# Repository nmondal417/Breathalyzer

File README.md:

# Breathalyzer Project Overview

The overall goal of this project is to create a wireless device that can be used to analyze the breath of medical patients to diagnose various diseases. The underlying technology is a graphene FET array. When the graphene FETs come into contact with different gases, the properties of the FETs will change. For example, the IDS vs VGS curve of the graphene FET may shift depending on the concentration of a certain gas molecule in the patient's breath. 

This GitHub project contains the PCBs and the code that are used to control and measure the graphene FET array. In simple terms, the PCB generates analog voltages VDS and VGS, and sends these to the graphene FET. Two multiplexers are used to select one particular FET out of the array. The PCB then measures the resulting IDS on that FET. This process is then repeated for every FET in the array, and then for different VDS and VGS. A python script can be used to plot the various voltage vs current curves.

# Device Design

The device is split into two chambers. The top chamber contains the graphene FET chip, an interface PCB for connecting to the chip, a humdity sensor, and a heater to prevent condensation on the chip. The bottom chamber contains most of the control electronics, inlucding the ESP32 micronctroller, the amplifiers, and multiplexers. There is also a single-cell 2 Ah LiPo for powering all the electronics, and a boost converter for specifically powering the heater. The LiPo can be charged through the USB-C connector located on the bottom of the device; when charging, the device will automatically turn off. 

On the outside of the device, there are various switches to control and LEDs to monitor the breathalyzer status. The main on switch connects the LiPo to the system and turns everything except the heater on; the heater on switch controls the heater. An RGB charge status LED lights up when the device is being charged; an orange light indicates that charging is occurring, while a white light indicates that charging is completed. Finally a "BLOW" LED controlled by the ESP32 indicates to the patient when they should blow into the device.

# PCBs

## ESP32 Carrier

https://github.com/nmondal417/Breathalyzer/tree/main/New%20PCB/Breathalyzer_ESP32

This PCB is where the ESP32, the main microcontroller, mounts **(NOTE: make sure to place the ESP32 correctly! the USB connector should face the side labeled "FRONT")**. The ESP32 controls the DAC, the ADC, and the multiplexers. It can also read data from the humidity sensor and the heater thermistor. It reports the current measurements in either serial or Bluetooth serial. 

The carrier board also contains the LiPo charge controller, the USB-C charging port, and the main 3.3V regulator that powers most of the ICs. All of the buttons and switches plug into the ESP32 carrrier board.

## Amplifier

https://github.com/nmondal417/Breathalyzer/tree/main/New%20PCB/Breathalyzer_Power%2BICs

This PCB contains the DAC, the ADC, and the op-amps that amplify the gate voltages.

The DAC (AD5328) communicates with the ESP32 over SPI. The DAC generates 6 gate voltages and 1 drain voltage. These voltages are in the range of 0 to 2 V; however, since the source voltage of this system is 1 V, the VGS and VDS voltages are actually -1 to +1 V. 

The op-amps then buffer and amplify the gate voltages. The op-amps can either provide x1 amplification (where it just acts a buffer), or x10 amplifcation. This amplification is controlled by the ESP32. The ESP32 controls two solid-state switches (ADG5433), which can change the amplifer gain by switching in a feedback resistor connected across the op-amp. The post-amplifcation gate voltage can be from -10 to +10 V.

The ADC (AD7274) communicates with the ESP32 over SPI. The ADC input is the voltage from the transimpedance amplifier. The ADC reads in range of 0 to 2V, and sends the ESP32 a 12-bit digital reading. 

This PCB also contains the 1V and 2V regulators that generate reference voltages for the DAC, ADC, and the op-amps, as well as a dual DC/DC converter (LT1945) that generates the -11V and +11V rails used for the amplifiers.

Finally, there is a mechanical switch that can completely disconnect the gate voltages from the graphene chip. This is useful for quickly turning off a voltage sweep, since if the incorrect gate voltages are accidentally applied the FET array can be destroyed.

## Multiplexer

https://github.com/nmondal417/Breathalyzer/tree/main/New%20PCB/Breathalyzer_Mux%2BConn

This PCB contains the two main multiplexers, the ribbon cable connector, and the transimpedance amplifier. 

The multiplexers are the ADG732. One is the drain demultiplexer, which sends the drain voltage to 1 of the 32 rows of the FET array. The other is the source muliplexer, which measures the source current from 1 of the 32 columns. 

The ribbon cable connector connects to the ribbon cable that runs from this PCB to the chip interface board. This cable is the PCB's connection to the drain, gate, and source terminals on the FET array.

The transimpedance ampliifer is an op-amp that is used to convert the source current measurement into a voltage. The formula is VMEAS = 1 - 1000*IDS, so an IDS of 100 uA would result in a VMEAS of 0.9V. This VMEAS is sent to the ADC.

# Code

All the code for this version of the breathlyzer is under 'New PCB code.' While the main code that runs on the ESP32 during normal operation is IV_Array_main_NEW, there are other files that test specific parts of the system, like the DAC and ADC, and are helpful for debugging.

## Blink

Simple test to just check if code can be uploaded correctly to the ESP32.

## ADC_DAC_test

This test can be used to test the ADC, DAC, or both together. Bascially, write analog voltages using the DAC and read an analog voltage using the ADC. If you are testing both the DAC and ADC at the same time, connect one of the DAC's output voltages to the input of the ADC.

## offset_and_gain_test

Used for checking and adjusting for the offset or gain error of the ADC and DAC. Test each DAC channel by connecting it to the ADC, and compare the read voltages to the expected values.

## gate_voltage_test

Tests that gate voltages can be generated properly. Combines the DAC code along with additional code to turn on the gate amplifier power supply and control the amplification.

## multiplexer_test

Close to a full system test, but instead of having the actual graphene array connected, you connect a test resistor between a drain connection on one mux and source connection on the other. When the correct select bits are sent to the muxes, the code should report the resistor value.

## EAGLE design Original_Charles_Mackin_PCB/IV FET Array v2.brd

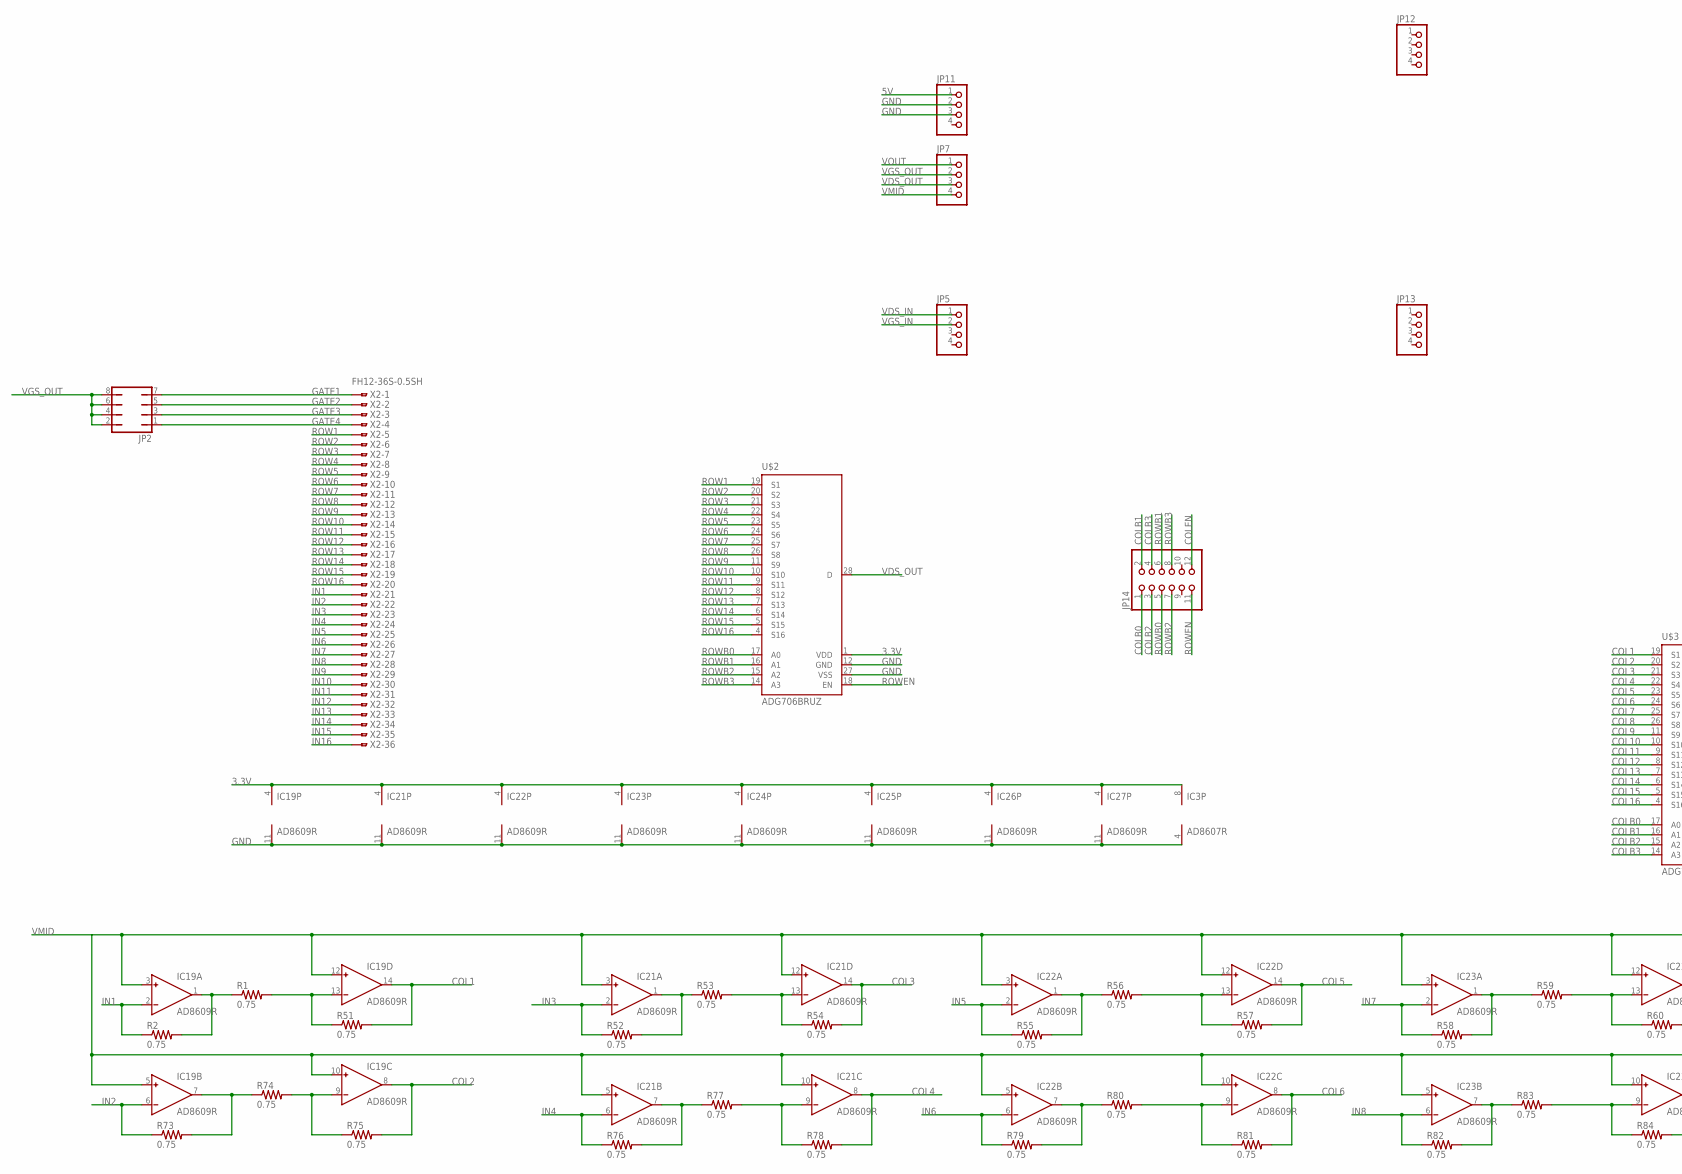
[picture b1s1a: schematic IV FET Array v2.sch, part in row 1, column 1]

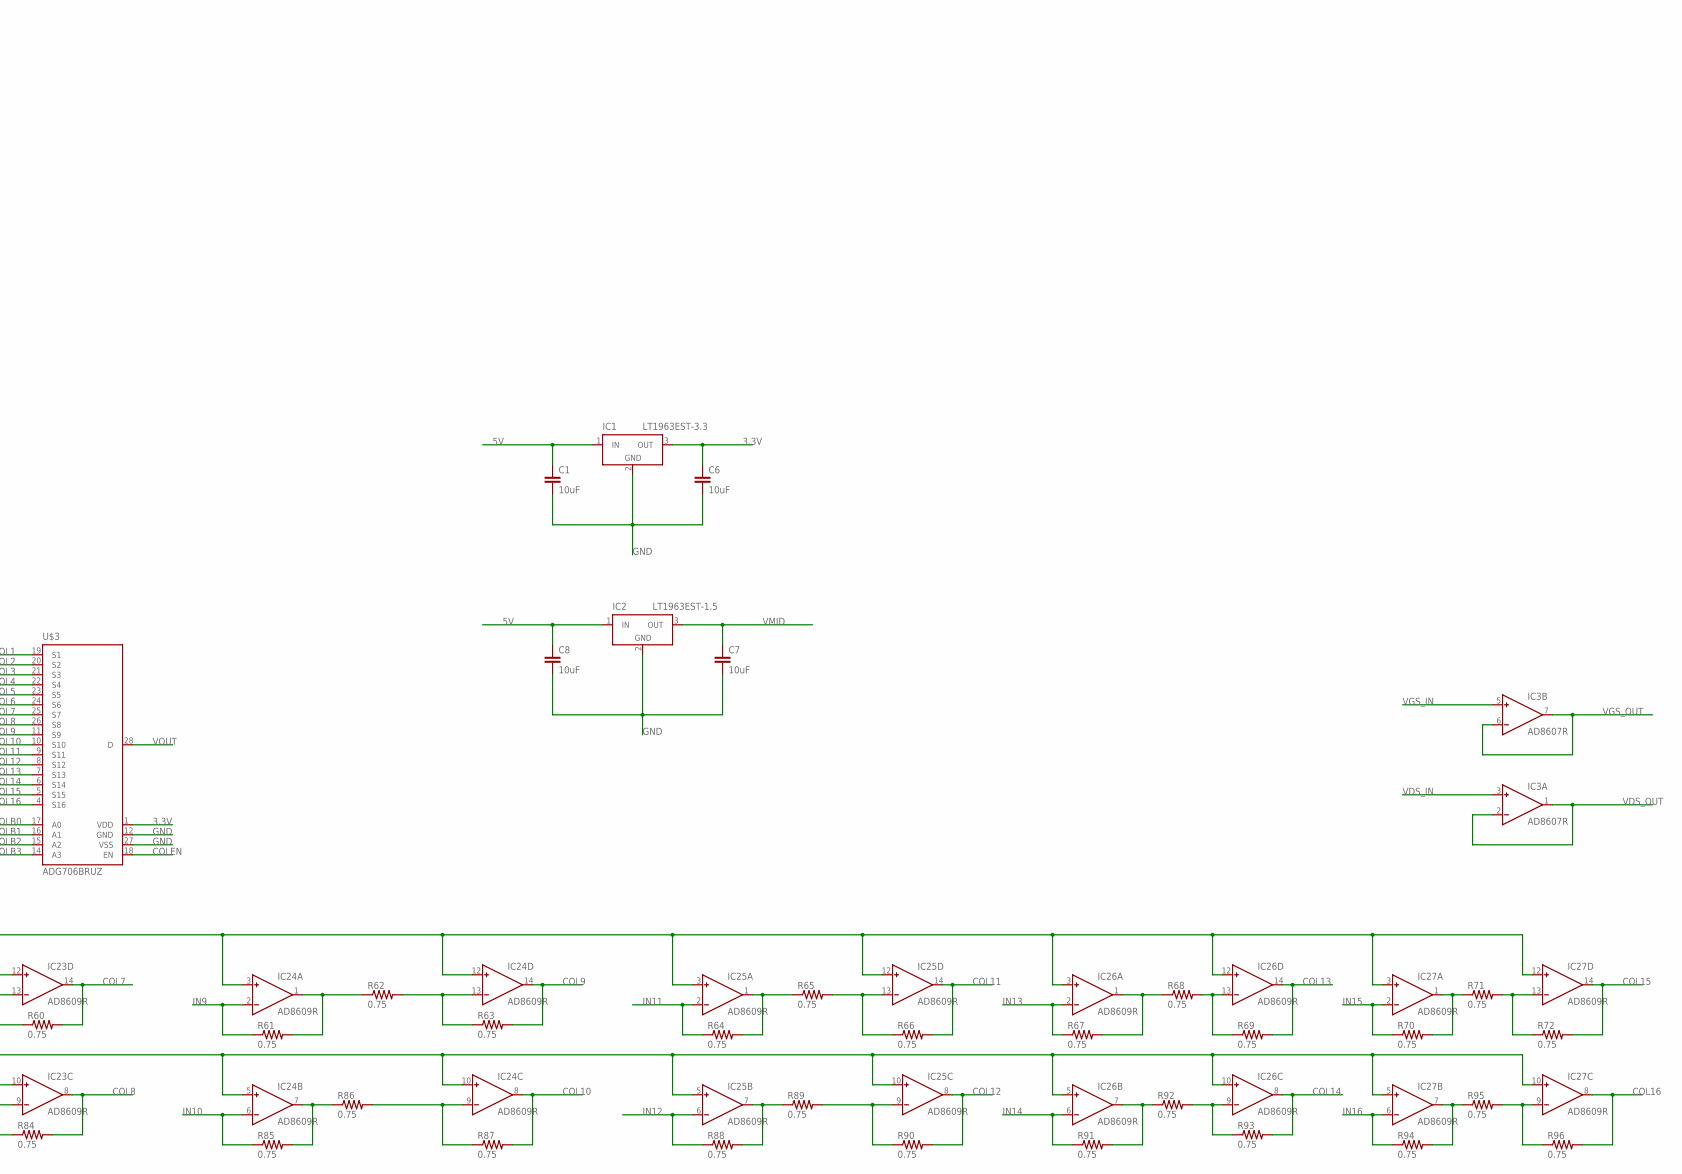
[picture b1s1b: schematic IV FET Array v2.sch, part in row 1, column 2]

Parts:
C1, C6, C7, C8: 10uF; 1210
IC1: LT1963EST-3.3; SOT223
IC2: LT1963EST-1.5; SOT223
IC3: AD8607R; SO8
IC19, IC21, IC22, IC23, IC24, IC25, IC26, IC27: AD8609R; SO14
JP2: JP4Q
JP5, JP7, JP11, JP12, JP13: PINHD-1X4; 1X04
JP14: PINHD-2X6; 2X06
R1, R2, R51, R52, R53, R54, R55, R56, R57, R58, R59, R60, R61, R62, R63, R64, R65, R66, R67, R68, R69, R70, R71, R72, R73, R74, R75, R76, R77, R78, R79, R80, R81, R82, R83, R84, R85, R86, R87, R88, R89, R90, R91, R92, R93, R94, R95, R96: 0.75; 0805
U$2, U$3: ADG706BRUZ; TSSOP28
X2: FH12-36S-0.5SH

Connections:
3.3V: C6.1, IC1.3 (OUT), IC3.8 (V+), IC19.4 (V+), IC21.4 (V+), IC22.4 (V+), IC23.4 (V+), IC24.4 (V+), IC25.4 (V+), IC26.4 (V+), IC27.4 (V+), U$2.1 (VDD), U$3.1 (VDD)
5V: C1.1, C8.1, IC1.1 (IN), IC2.1 (IN), JP11.1
COL1: IC19.14 (OUT), R51.2, U$3.19 (S1)
COL2: IC19.8 (OUT), R75.2, U$3.20 (S2)
COL3: IC21.14 (OUT), R54.2, U$3.21 (S3)
COL4: IC21.8 (OUT), R78.2, U$3.22 (S4)
COL5: IC22.14 (OUT), R57.2, U$3.23 (S5)
COL6: IC22.8 (OUT), R81.2, U$3.24 (S6)
COL7: IC23.14 (OUT), R60.2, U$3.25 (S7)
COL8: IC23.8 (OUT), R84.2, U$3.26 (S8)
COL9: IC24.14 (OUT), R63.2, U$3.11 (S9)
COL10: IC24.8 (OUT), R87.2, U$3.10 (S10)
COL11: IC25.14 (OUT), R66.2, U$3.9 (S11)
COL12: IC25.8 (OUT), R90.2, U$3.8 (S12)
COL13: IC26.14 (OUT), R69.2, U$3.7 (S13)
COL14: IC26.8 (OUT), R93.2, U$3.6 (S14)
COL15: IC27.14 (OUT), R72.2, U$3.5 (S15)
COL16: IC27.8 (OUT), R96.2, U$3.4 (S16)
COLB0: JP14.1, U$3.17 (A0)
COLB1: JP14.2, U$3.16 (A1)
COLB2: JP14.3, U$3.15 (A2)
COLB3: JP14.4, U$3.14 (A3)
COLEN: JP14.12, U$3.18 (EN)
GATE1: JP2.7, X2.1
GATE2: JP2.5, X2.2
GATE3: JP2.3, X2.3
GATE4: JP2.1, X2.4
GND: C1.2, C6.2, C7.2, C8.2, IC1.2 (GND), IC1.4 (GND), IC2.2 (GND), IC2.4 (GND), IC3.4 (V-), IC19.11 (V-), IC21.11 (V-), IC22.11 (V-), IC23.11 (V-), IC24.11 (V-), IC25.11 (V-), IC26.11 (V-), IC27.11 (V-), JP11.2, JP11.3, U$2.12 (GND), U$2.27 (VSS), U$3.12 (GND), U$3.27 (VSS)
IN1: IC19.2 (IN-), R2.1, X2.21
IN2: IC19.6 (IN-), R73.1, X2.22
IN3: IC21.2 (IN-), R52.1, X2.23
IN4: IC21.6 (IN-), R76.1, X2.24
IN5: IC22.2 (IN-), R55.1, X2.25
IN6: IC22.6 (IN-), R79.1, X2.26
IN7: IC23.2 (IN-), R58.1, X2.27
IN8: IC23.6 (IN-), R82.1, X2.28
IN9: IC24.2 (IN-), R61.1, X2.29
IN10: IC24.6 (IN-), R85.1, X2.30
IN11: IC25.2 (IN-), R64.1, X2.31
IN12: IC25.6 (IN-), R88.1, X2.32
IN13: IC26.2 (IN-), R67.1, X2.33
IN14: IC26.6 (IN-), R91.1, X2.34
IN15: IC27.2 (IN-), R70.1, X2.35
IN16: IC27.6 (IN-), R94.1, X2.36
unnamed: IC25.1 (OUT), R64.2, R65.1
unnamed: IC25.13 (IN-), R65.2, R66.1
unnamed: IC24.1 (OUT), R61.2, R62.1
unnamed: IC24.13 (IN-), R62.2, R63.1
unnamed: IC25.7 (OUT), R88.2, R89.1
unnamed: IC25.9 (IN-), R89.2, R90.1
unnamed: IC24.9 (IN-), R86.2, R87.1
unnamed: IC24.7 (OUT), R85.2, R86.1
unnamed: IC19.1 (OUT), R1.1, R2.2
unnamed: IC19.7 (OUT), R73.2, R74.1
unnamed: IC19.9 (IN-), R74.2, R75.1
unnamed: IC19.13 (IN-), R1.2, R51.1
unnamed: IC23.13 (IN-), R59.2, R60.1
unnamed: IC23.1 (OUT), R58.2, R59.1
unnamed: IC21.1 (OUT), R52.2, R53.1
unnamed: IC21.13 (IN-), R53.2, R54.1
unnamed: IC22.1 (OUT), R55.2, R56.1
unnamed: IC22.13 (IN-), R56.2, R57.1
unnamed: IC23.9 (IN-), R83.2, R84.1
unnamed: IC23.7 (OUT), R82.2, R83.1
unnamed: IC22.9 (IN-), R80.2, R81.1
unnamed: IC22.7 (OUT), R79.2, R80.1
unnamed: IC21.9 (IN-), R77.2, R78.1
unnamed: IC21.7 (OUT), R76.2, R77.1
unnamed: IC26.1 (OUT), R67.2, R68.1
unnamed: IC26.13 (IN-), R68.2, R69.1
unnamed: IC26.9 (IN-), R92.2, R93.1
unnamed: IC26.7 (OUT), R91.2, R92.1
unnamed: IC27.7 (OUT), R94.2, R95.1
unnamed: IC27.9 (IN-), R95.2, R96.1
unnamed: IC27.13 (IN-), R71.2, R72.1
unnamed: IC27.1 (OUT), R70.2, R71.1
ROW1: U$2.19 (S1), X2.5
ROW2: U$2.20 (S2), X2.6
ROW3: U$2.21 (S3), X2.7
ROW4: U$2.22 (S4), X2.8
ROW5: U$2.23 (S5), X2.9
ROW6: U$2.24 (S6), X2.10
ROW7: U$2.25 (S7), X2.11
ROW8: U$2.26 (S8), X2.12
ROW9: U$2.11 (S9), X2.13
ROW10: U$2.10 (S10), X2.14
ROW11: U$2.9 (S11), X2.15
ROW12: U$2.8 (S12), X2.16
ROW13: U$2.7 (S13), X2.17
ROW14: U$2.6 (S14), X2.18
ROW15: U$2.5 (S15), X2.19
ROW16: U$2.4 (S16), X2.20
ROWB0: JP14.5, U$2.17 (A0)
ROWB1: JP14.6, U$2.16 (A1)
ROWB2: JP14.7, U$2.15 (A2)
ROWB3: JP14.8, U$2.14 (A3)
ROWEN: JP14.11, U$2.18 (EN)
VDS_IN: IC3.3 (IN+), JP5.1
VDS_OUT: IC3.1 (OUT), IC3.2 (IN-), JP7.3, U$2.28 (D)
VGS_IN: IC3.5 (IN+), JP5.2
VGS_OUT: IC3.6 (IN-), IC3.7 (OUT), JP2.2, JP2.4, JP2.6, JP2.8, JP7.2
VMID: C7.1, IC2.3 (OUT), IC19.3 (IN+), IC19.5 (IN+), IC19.10 (IN+), IC19.12 (IN+), IC21.3 (IN+), IC21.5 (IN+), IC21.10 (IN+), IC21.12 (IN+), IC22.3 (IN+), IC22.5 (IN+), IC22.10 (IN+), IC22.12 (IN+), IC23.3 (IN+), IC23.5 (IN+), IC23.10 (IN+), IC23.12 (IN+), IC24.3 (IN+), IC24.5 (IN+), IC24.10 (IN+), IC24.12 (IN+), IC25.3 (IN+), IC25.5 (IN+), IC25.10 (IN+), IC25.12 (IN+), IC26.3 (IN+), IC26.5 (IN+), IC26.10 (IN+), IC26.12 (IN+), IC27.3 (IN+), IC27.5 (IN+), IC27.10 (IN+), IC27.12 (IN+), JP7.4
VOUT: JP7.1, U$3.28 (D)

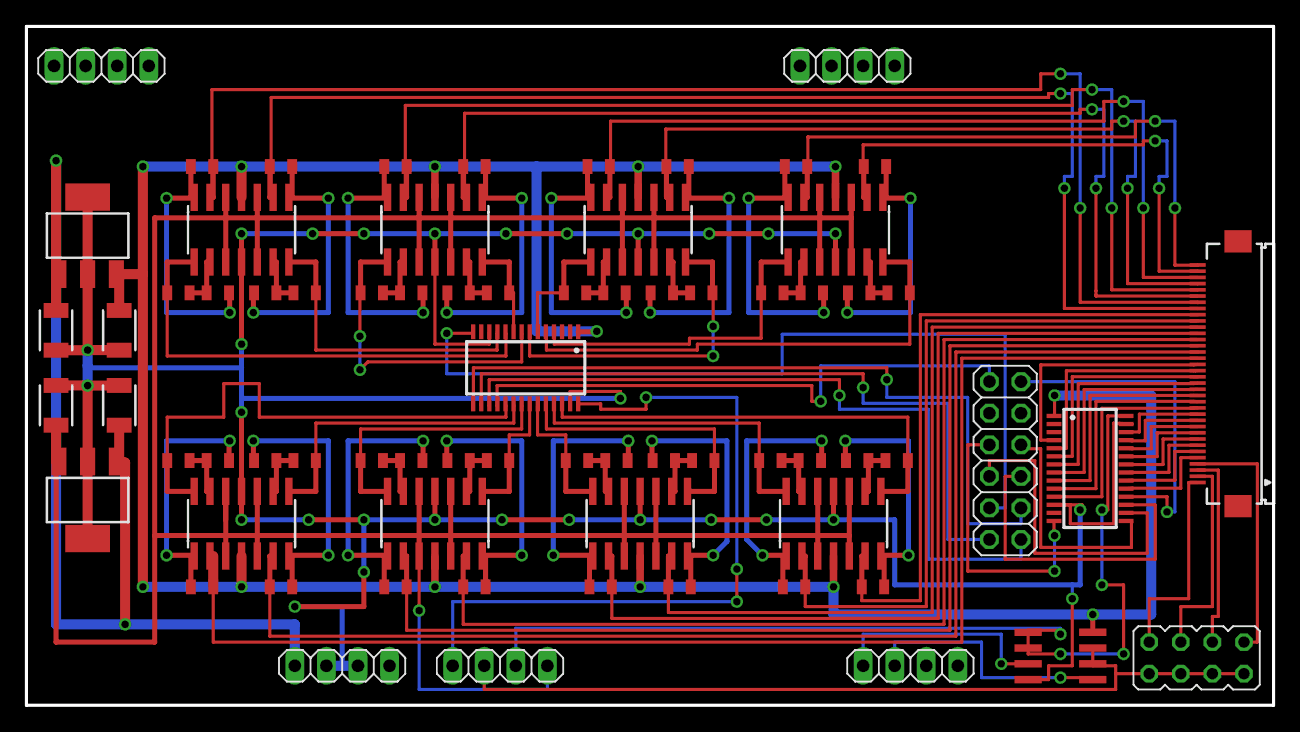
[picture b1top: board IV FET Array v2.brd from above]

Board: 2 copper layers, 100.3 x 54.6 mm, 73 parts (0 on the bottom side), 103 nets.

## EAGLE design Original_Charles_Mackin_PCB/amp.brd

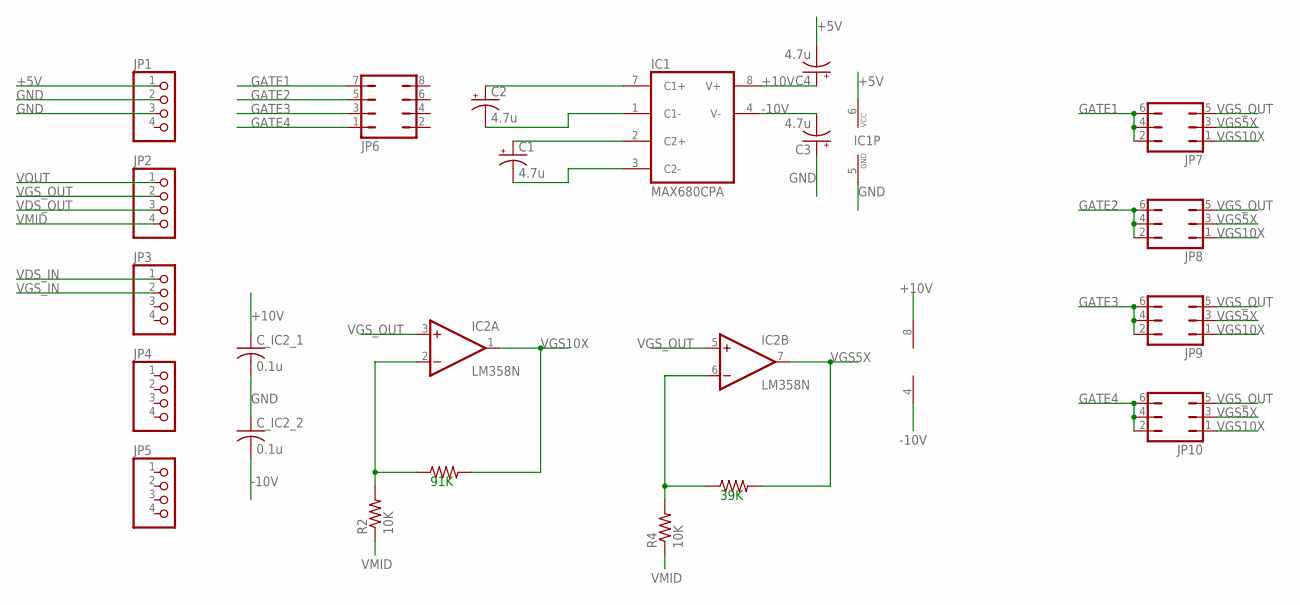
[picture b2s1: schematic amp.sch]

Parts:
C1, C2, C3, C4: 4.7u; B45181B
C_IC2_1, C_IC2_2: 0.1u; C025-024X044
IC1: MAX680CPA; DIL08
IC2: LM358N; DIL08
JP1, JP2, JP3, JP4, JP5: PINHD-1X4; 1X04
JP6: JP4Q
JP7, JP8, JP9, JP10: JP3Q
R1: 91K; 0204/7
R2, R4: 10K; 0204/7
R3: 39K; 0204/7

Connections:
+5V: C4.-, IC1.6 (VCC), JP1.1
+10V: C4.+, C_IC2_1.1, IC1.8 (V+), IC2.8 (V+)
-10V: C3.-, C_IC2_2.2, IC1.4 (V-), IC2.4 (V-)
GATE1: JP6.7, JP7.2, JP7.4, JP7.6
GATE2: JP6.5, JP8.2, JP8.4, JP8.6
GATE3: JP6.3, JP9.2, JP9.4, JP9.6
GATE4: JP6.1, JP10.2, JP10.4, JP10.6
GND: C3.+, C_IC2_1.2, C_IC2_2.1, IC1.5 (GND), JP1.2, JP1.3
unnamed: C2.+, IC1.7 (C1+)
unnamed: C2.-, IC1.1 (C1-)
unnamed: C1.+, IC1.2 (C2+)
unnamed: C1.-, IC1.3 (C2-)
unnamed: IC2.2 (-IN), R1.1, R2.2
unnamed: IC2.6 (-IN), R3.1, R4.2
VDS_IN: JP3.1
VDS_OUT: JP2.3
VGS5X: IC2.7 (OUT), JP7.3, JP8.3, JP9.3, JP10.3, R3.2
VGS10X: IC2.1 (OUT), JP7.1, JP8.1, JP9.1, JP10.1, R1.2
VGS_IN: JP3.2
VGS_OUT: IC2.3 (+IN), IC2.5 (+IN), JP2.2, JP7.5, JP8.5, JP9.5, JP10.5
VMID: JP2.4, R2.1, R4.1
VOUT: JP2.1

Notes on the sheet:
91K
39K

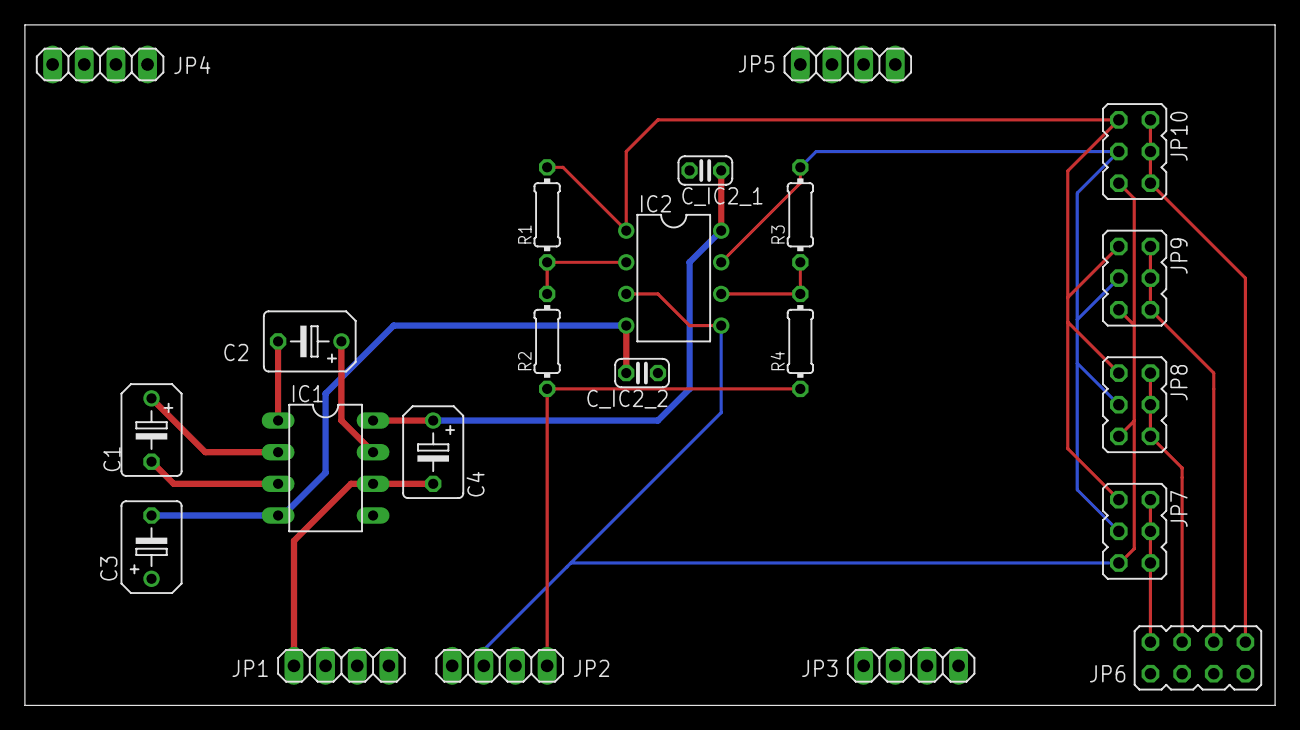
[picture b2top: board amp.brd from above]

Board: 2 copper layers, 100.3 x 54.6 mm, 22 parts (0 on the bottom side), 18 nets.

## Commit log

2022-03-22 added PCB
2022-04-03 incorporated Jaeyoung's design
2022-04-04 changed to LT1945, 1v ref LDO
2022-04-05 aded thresholds back, added testpoints, created top level sheet
2022-04-06 switched -20V and +20V around
2022-04-09 changed to 0805 components
2022-04-13 layout of components, testing DAC SPI code with multiple SPI slaves
2022-04-20 routed everything except multiplexers
2022-04-21 routed multiplexers to small connector
2022-04-23 added some silkscreen text
2022-04-23 connected stuff to ground
2022-04-26 added global switch and 80- and 60-pin connectors
2022-04-26 finished routing, no drc errors
2022-04-27 added name, white boxes above and below global switch
2022-04-28 random stuff: changing 0603's to 0805, changing out transimp amp, etc
2022-04-28 made interface board
2022-05-01 boost converter shutdown control, silk, and rounded corners
2022-05-01 generated gerbers
2022-05-02 committing before messing with internal layers
2022-05-03 increased via size from 20 to 24 mils
2022-06-07 updated test code
2022-06-13 updates to main code and started python script
2023-02-07 massive file update
2023-02-11 added testpoints to PCBs, and global gate switch
2023-02-14 finalized new iv_array code, also fixed DRC errors on ESP32 board
2023-02-14 started routing the second board
2023-03-05 added humidity sensor, heater circuit, rerouted
2023-03-12 started routing bottom board
2023-03-28 PCBs nearing completion
2023-03-29 PCBs finalized, main change was JST battery connector flip
2023-04-05 generated gerbers, also started writing new code
2023-04-10 some changes to boost pcb (moving r1, adding silk)
2023-05-23 file reorg
2023-05-23 added test plan, power flow, and drawing
2023-05-31 added old PCB stuff from Charles

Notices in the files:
parts and their libraries:
SparkFun-Capacitors: Licensing: Creative Commons ShareAlike 4.0 International - https://creativecommons.org/licenses/by-sa/4.0
